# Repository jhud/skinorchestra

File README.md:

# Skin Orchestra
Turn an Android phone into a MIDI/OSC skin touch sensor with this simple, tiny, battery-free circuit.

An EAGLE board design. I made this years ago and have moved onto KiCAD and SMD since. We have also moved onto a pure digital touch sensor design integrated with our wearable LED costumes, so this circuit is not likely to be under active development again.

However, it's been tested with many different Android phones, and works well in practice. You might want to use the "phantom power" idea to run other devices off a microphone port without needing batteries.

## Concept

This circuit is an oscillator which runs on the bias voltage that can be extracted from an Android smartphone's microphone jack. Therefore, a low current CMOS 555 timer must be used. Check your phone's specifications before connecting this circuit - you use it completely at your own risk.

Once plugged into an Android phone, the pads marked "skin" can be bridged by skin contact, which produces a variable frequency square wave across the microphone input.

You can use this "as is" for a simple tone, but this signal can also be processed by an Android app, which counts the zero-crossing frequency of the square wave and converts it to MIDI or OSC (app coming soon).

## Construction

This board design only uses a few through-hole components, so it should be easy to construct. You could also build it easily with veroboard or on a breadboard if you don't want to fabricate the board.

To connect to the smartphone, use a standard 4-pin headphone/microphone connector. Connect ground to ground, and the microphone to "SIGNAL". Check your phone's headphone jack pinout to make sure you have the right channels on the connector.

## Usage

You can give one wire to somebody else, and hold the other yourself. The harder you squeeze them, the higher the notes will be from the circuit.

## Safety

Use this design at your own risk. Do not plug the phone into a charger and then connect it to someone - there should never be a conductive connection between a person's body and a device wired to mains power.

## Acknowledgements

This project is a concept developed by Alma Edelstein-Feinsilber, James Hudson, and Patricio Zarazaga, to allow skin-touch control of musical instruments in 2014.

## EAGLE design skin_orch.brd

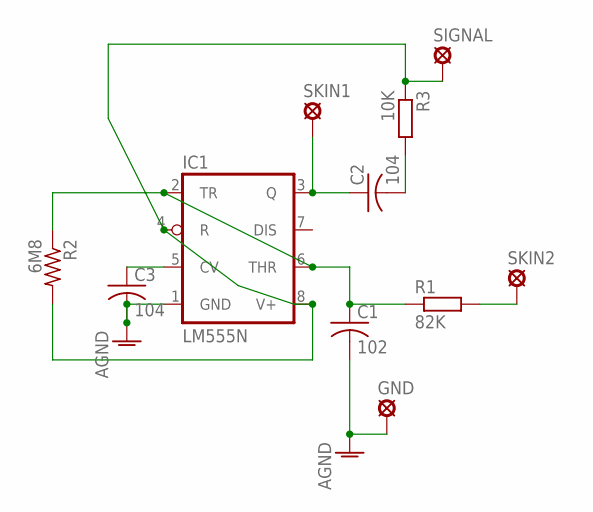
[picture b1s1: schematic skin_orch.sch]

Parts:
C1: 102; C025-030X050
C2, C3: 104; C025-030X050
GND: LSP10
IC1: LM555N; DIL08
R1: 82K; 0207/2V
R2: 6M8; 0207/7
R3: 10K; 0207/2V
SIGNAL: LSP10
SKIN1, SKIN2: LSP10

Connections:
AGND: C1.2, C3.2, GND.MP, IC1.1 (GND)
unnamed: R1.2, SKIN2.MP
unnamed: C3.1, IC1.5 (CV)
unnamed: IC1.4 (R), IC1.8 (V+), R2.2, R3.1, SIGNAL.MP
unnamed: C2.1, IC1.3 (Q), SKIN1.MP
unnamed: C2.2, R3.2
unnamed: C1.1, IC1.2 (TR), IC1.6 (THR), R1.1, R2.1

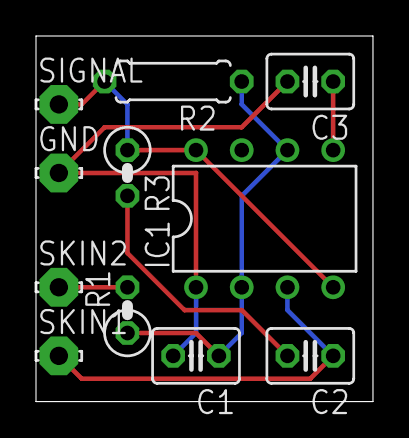
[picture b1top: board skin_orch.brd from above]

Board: 2 copper layers, 18.7 x 20.3 mm, 11 parts (0 on the bottom side), 7 nets.

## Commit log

2020-10-20 Cropped image.
2020-10-22 Updated the instructions and added a photo.
